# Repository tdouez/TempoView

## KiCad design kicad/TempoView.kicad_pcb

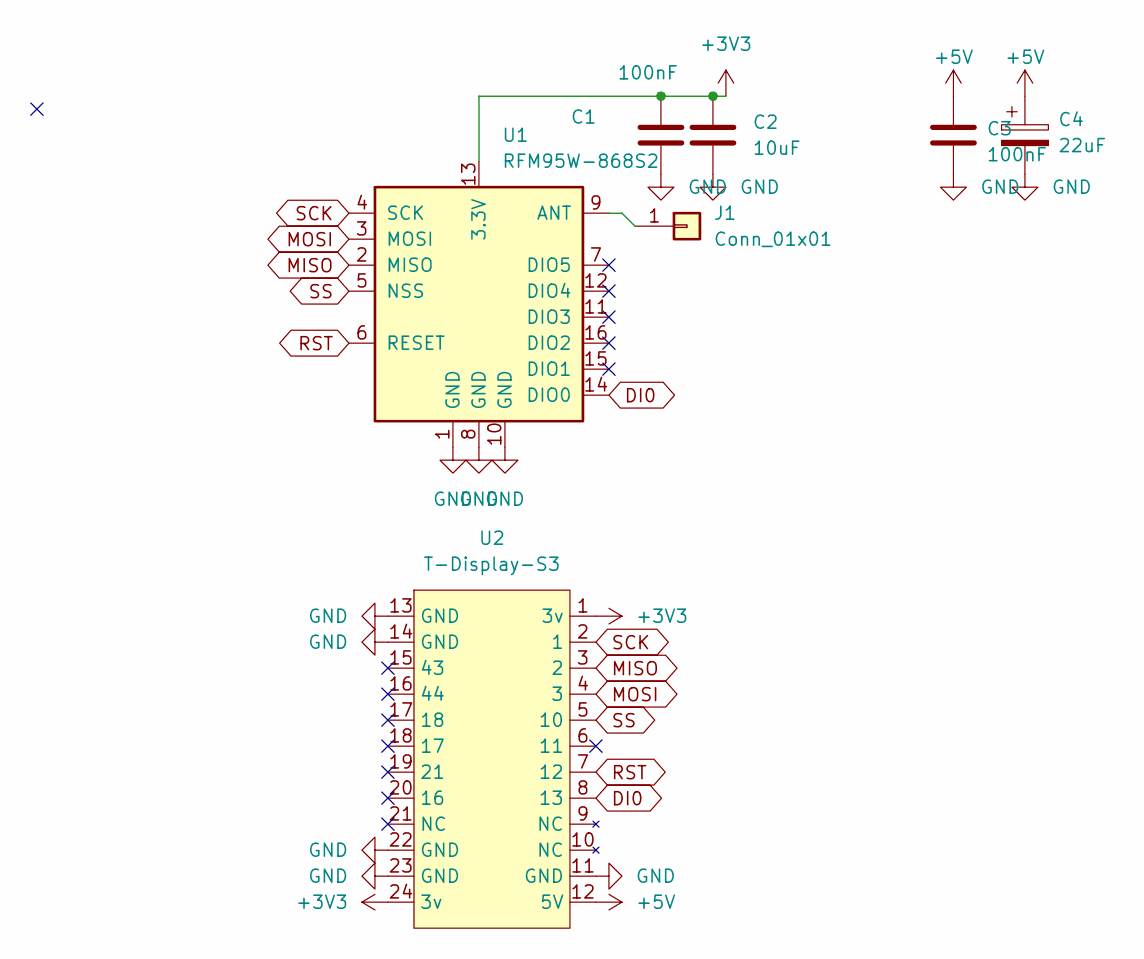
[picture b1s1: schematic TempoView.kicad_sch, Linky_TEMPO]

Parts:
C1, C3: 100nF; C_Disc_D4.3mm_W1.9mm_P5.00mm
C2: 10uF; CP_Radial_D4.0mm_P2.00mm
C4: 22uF; CP_Radial_D4.0mm_P2.00mm
J1: Conn_01x01; PinHeader_1x01_P2.54mm_Vertical
U1: RFM95W-868S2; HOPERF_RFM9XW_THT
U2: T-Display-S3

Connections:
+3V3: C1.2, C2.1, U1.13 (3.3V), U2.1 (3v), U2.24 (3v)
+5V: C3.1, C4.1, U2.12 (5V)
DI0: U1.14 (DIO0), U2.8 (13)
GND: C1.1, C2.2, C3.2, C4.2, U1.1 (GND), U1.8 (GND), U1.10 (GND), U2.11 (GND), U2.13 (GND), U2.14 (GND), U2.22 (GND), U2.23 (GND)
MISO: U1.2 (MISO), U2.3 (2)
MOSI: U1.3 (MOSI), U2.4 (3)
unnamed: J1.1, U1.9 (ANT)
RST: U1.6 (RESET), U2.7 (12)
SCK: U1.4 (SCK), U2.2 (1)
SS: U1.5 (NSS), U2.5 (10)

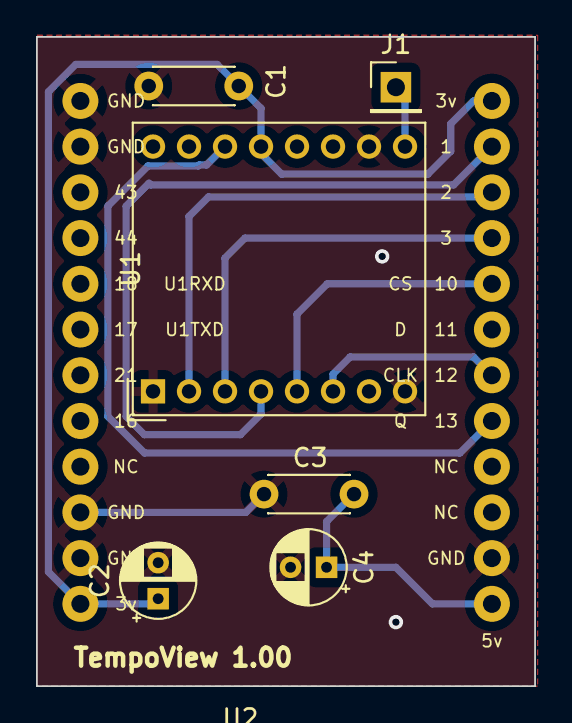
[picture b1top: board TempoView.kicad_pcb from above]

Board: 2 copper layers, 27.7 x 36.1 mm, 7 parts (0 on the bottom side), 10 nets.

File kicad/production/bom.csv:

Designator,Footprint,Quantity,Value,LCSC Part #
"C1, C3",C_Disc_D4.3mm_W1.9mm_P5.00mm,2,100nF,
C2,CP_Radial_D4.0mm_P2.00mm,1,10uF,
C4,CP_Radial_D4.0mm_P2.00mm,1,22uF,
J1,PinHeader_1x01_P2.54mm_Vertical,1,Conn_01x01,
U1,HOPERF_RFM9XW_THT,1,RFM95W-868S2,
U2,T-Display-S3,1,T-Display-S3,

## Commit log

2025-11-16 v1.0.0
